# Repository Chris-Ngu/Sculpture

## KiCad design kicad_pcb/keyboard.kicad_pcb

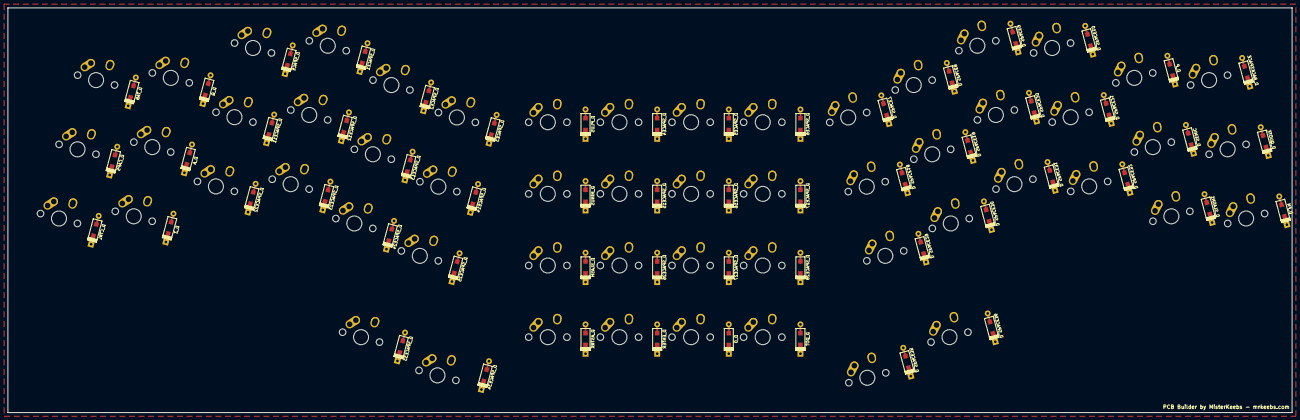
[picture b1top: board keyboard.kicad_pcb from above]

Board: 2 copper layers, 341.5 x 107.6 mm, 112 parts (0 on the bottom side), 76 nets, no tracks yet.

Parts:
D_0: D; D_SOD123_axial
D_A: D; D_SOD123_axial
D_ASTRK: D; D_SOD123_axial
D_BACKSPACE: D; D_SOD123_axial
D_CAPS: D; D_SOD123_axial
D_CTRL: D; D_SOD123_axial
D_DOT: D; D_SOD123_axial
D_ENTER: D; D_SOD123_axial
D_FN: D; D_SOD123_axial
D_MINUS: D; D_SOD123_axial
D_P: D; D_SOD123_axial
D_PLUS: D; D_SOD123_axial
D_Q: D; D_SOD123_axial
D_QUOTE: D; D_SOD123_axial
D_SEMIC: D; D_SOD123_axial
D_SLASH, D_SLASH1: D; D_SOD123_axial
D_SPACE, D_SPACE1, D_SPACE2, D_SPACE3, D_SPACE4, D_SPACE5, D_SPACE6, D_SPACE7, D_SPACE8, D_SPACE9, D_SPACE10, D_SPACE11, D_SPACE12, D_SPACE13, D_SPACE14, D_SPACE15, D_SPACE16, D_SPACE17, D_SPACE18, D_SPACE19, D_SPACE20, D_SPACE21, D_SPACE22, D_SPACE23, D_SPACE24, D_SPACE25, D_SPACE26, D_SPACE27, D_SPACE28, D_SPACE29, D_SPACE30, D_SPACE31, D_SPACE32, D_SPACE33, D_SPACE34, D_SPACE35, D_SPACE36: D; D_SOD123_axial
D_TAB: D; D_SOD123_axial
D_Z: D; D_SOD123_axial
K_0: KEYSW; MX-1U-NoLED
K_A: KEYSW; MX-1U-NoLED
K_ASTRK: KEYSW; MX-1U-NoLED
K_BACKSPACE: KEYSW; MX-1U-NoLED
K_CAPS: KEYSW; MX-1U-NoLED
K_CTRL: KEYSW; MX-1U-NoLED
K_DOT: KEYSW; MX-1U-NoLED
K_ENTER: KEYSW; MX-1U-NoLED
K_FN: KEYSW; MX-1U-NoLED
K_MINUS: KEYSW; MX-1U-NoLED
K_P: KEYSW; MX-1U-NoLED
K_PLUS: KEYSW; MX-1U-NoLED
K_Q: KEYSW; MX-1U-NoLED
K_QUOTE: KEYSW; MX-1U-NoLED
K_SEMIC: KEYSW; MX-1U-NoLED
K_SLASH, K_SLASH1: KEYSW; MX-1U-NoLED
K_SPACE, K_SPACE1, K_SPACE2, K_SPACE3, K_SPACE4, K_SPACE5, K_SPACE6, K_SPACE7, K_SPACE8, K_SPACE9, K_SPACE10, K_SPACE11, K_SPACE12, K_SPACE13, K_SPACE14, K_SPACE15, K_SPACE16, K_SPACE17, K_SPACE18, K_SPACE19, K_SPACE20, K_SPACE21, K_SPACE22, K_SPACE23, K_SPACE24, K_SPACE25, K_SPACE26, K_SPACE27, K_SPACE28, K_SPACE29, K_SPACE30, K_SPACE31, K_SPACE32, K_SPACE33, K_SPACE34, K_SPACE35, K_SPACE36: KEYSW; MX-1U-NoLED
K_TAB: KEYSW; MX-1U-NoLED
K_Z: KEYSW; MX-1U-NoLED

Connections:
/col0: K_CAPS.1, K_CTRL.1, K_TAB.1
/col1: K_A.1, K_Q.1, K_Z.1
/col2: K_SPACE.1, K_SPACE11.1, K_SPACE22.1
/col3: K_SPACE1.1, K_SPACE12.1, K_SPACE23.1
/col4: K_SPACE2.1, K_SPACE13.1, K_SPACE24.1, K_SPACE33.1
/col5: K_SPACE3.1, K_SPACE14.1, K_SPACE25.1, K_SPACE34.1
/col6: K_ASTRK.1, K_MINUS.1, K_PLUS.1, K_SLASH.1
/col7: K_ENTER.1, K_SPACE4.1, K_SPACE15.1, K_SPACE26.1
/col8: K_0.1, K_SPACE5.1, K_SPACE16.1, K_SPACE27.1
/col9: K_DOT.1, K_SPACE6.1, K_SPACE17.1, K_SPACE28.1
/col10: K_SPACE7.1, K_SPACE18.1, K_SPACE29.1, K_SPACE35.1
/col11: K_SPACE8.1, K_SPACE19.1, K_SPACE30.1, K_SPACE36.1
/col12: K_SPACE9.1, K_SPACE20.1, K_SPACE31.1
/col13: K_SPACE10.1, K_SPACE21.1, K_SPACE32.1
/col14: K_P.1, K_SEMIC.1, K_SLASH1.1
/col15: K_BACKSPACE.1, K_FN.1, K_QUOTE.1
/row0: D_BACKSPACE.1, D_P.1, D_PLUS.1, D_Q.1, D_SPACE.1, D_SPACE1.1, D_SPACE2.1, D_SPACE3.1, D_SPACE4.1, D_SPACE5.1, D_SPACE6.1, D_SPACE7.1, D_SPACE8.1, D_SPACE9.1, D_SPACE10.1, D_TAB.1
/row1: D_A.1, D_CAPS.1, D_MINUS.1, D_QUOTE.1, D_SEMIC.1, D_SPACE11.1, D_SPACE12.1, D_SPACE13.1, D_SPACE14.1, D_SPACE15.1, D_SPACE16.1, D_SPACE17.1, D_SPACE18.1, D_SPACE19.1, D_SPACE20.1, D_SPACE21.1
/row2: D_CTRL.1, D_FN.1, D_SLASH.1, D_SLASH1.1, D_SPACE22.1, D_SPACE23.1, D_SPACE24.1, D_SPACE25.1, D_SPACE26.1, D_SPACE27.1, D_SPACE28.1, D_SPACE29.1, D_SPACE30.1, D_SPACE31.1, D_SPACE32.1, D_Z.1
/row3: D_0.1, D_ASTRK.1, D_DOT.1, D_ENTER.1, D_SPACE33.1, D_SPACE34.1, D_SPACE35.1, D_SPACE36.1
unnamed: D_0.2, K_0.2
unnamed: D_A.2, K_A.2
unnamed: D_ASTRK.2, K_ASTRK.2
unnamed: D_BACKSPACE.2, K_BACKSPACE.2
unnamed: D_CAPS.2, K_CAPS.2
unnamed: D_CTRL.2, K_CTRL.2
unnamed: D_DOT.2, K_DOT.2
unnamed: D_ENTER.2, K_ENTER.2
unnamed: D_FN.2, K_FN.2
unnamed: D_MINUS.2, K_MINUS.2
unnamed: D_P.2, K_P.2
unnamed: D_PLUS.2, K_PLUS.2
unnamed: D_Q.2, K_Q.2
unnamed: D_QUOTE.2, K_QUOTE.2
unnamed: D_SEMIC.2, K_SEMIC.2
unnamed: D_SLASH1.2, K_SLASH1.2
unnamed: D_SLASH.2, K_SLASH.2
unnamed: D_SPACE1.2, K_SPACE1.2
unnamed: D_SPACE2.2, K_SPACE2.2
unnamed: D_SPACE3.2, K_SPACE3.2
unnamed: D_SPACE4.2, K_SPACE4.2
unnamed: D_SPACE5.2, K_SPACE5.2
unnamed: D_SPACE6.2, K_SPACE6.2
unnamed: D_SPACE7.2, K_SPACE7.2
unnamed: D_SPACE8.2, K_SPACE8.2
unnamed: D_SPACE9.2, K_SPACE9.2
unnamed: D_SPACE10.2, K_SPACE10.2
unnamed: D_SPACE11.2, K_SPACE11.2
unnamed: D_SPACE12.2, K_SPACE12.2
unnamed: D_SPACE13.2, K_SPACE13.2
unnamed: D_SPACE14.2, K_SPACE14.2
unnamed: D_SPACE15.2, K_SPACE15.2
unnamed: D_SPACE16.2, K_SPACE16.2
unnamed: D_SPACE17.2, K_SPACE17.2
unnamed: D_SPACE18.2, K_SPACE18.2
unnamed: D_SPACE19.2, K_SPACE19.2
unnamed: D_SPACE20.2, K_SPACE20.2
unnamed: D_SPACE21.2, K_SPACE21.2
unnamed: D_SPACE22.2, K_SPACE22.2
unnamed: D_SPACE23.2, K_SPACE23.2
unnamed: D_SPACE24.2, K_SPACE24.2
unnamed: D_SPACE25.2, K_SPACE25.2
unnamed: D_SPACE26.2, K_SPACE26.2
unnamed: D_SPACE27.2, K_SPACE27.2
unnamed: D_SPACE28.2, K_SPACE28.2
unnamed: D_SPACE29.2, K_SPACE29.2
unnamed: D_SPACE30.2, K_SPACE30.2
unnamed: D_SPACE31.2, K_SPACE31.2
unnamed: D_SPACE32.2, K_SPACE32.2
unnamed: D_SPACE33.2, K_SPACE33.2
unnamed: D_SPACE34.2, K_SPACE34.2
unnamed: D_SPACE35.2, K_SPACE35.2
unnamed: D_SPACE36.2, K_SPACE36.2
unnamed: D_SPACE.2, K_SPACE.2
unnamed: D_TAB.2, K_TAB.2
unnamed: D_Z.2, K_Z.2

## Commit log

2022-10-17 adding kle layout from planning work
2022-10-19 adding files
2022-10-19 deleting components to add pro micro
2022-10-19 adding silkscreen content
2022-10-23 rotating alphas
